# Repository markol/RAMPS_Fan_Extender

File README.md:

##Fan extension board for RAMPS##
This extension allows you to connect additional 4 fans into RAMPS board (plugged into servo pins). Board is single sided and was designed for home etching, uses THT and SMD soldering components. Make sure board dimensions (16x40mm) are not colliding with your actual setup. NPN transistors can be used as well instead of FET's. Voltage above 5V is provided by additional connector plug, reversed polarity may destory electronics.
Configuration process is similar to other boards, example [here](https://www.geeetech.com/wiki/index.php/Reprap_Ramps1.4_RRD_Fan_Extender), use pins 11, 6, 5 or 4. Made with KiCAD.

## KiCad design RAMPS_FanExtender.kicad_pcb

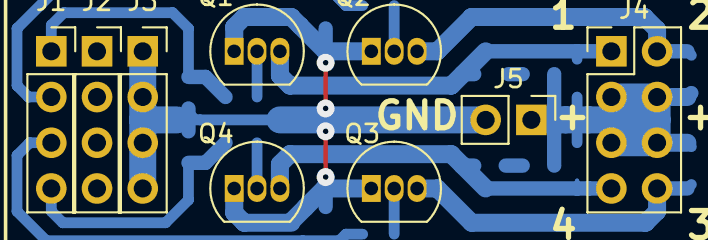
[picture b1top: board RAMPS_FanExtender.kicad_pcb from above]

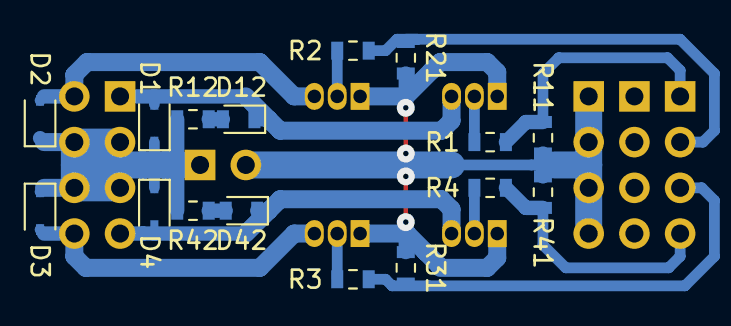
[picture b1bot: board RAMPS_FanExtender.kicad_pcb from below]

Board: 2 copper layers, 25 parts (16 on the bottom side), 16 nets.

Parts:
D1, D2, D3, D4: 1N4148WS; D_SOD-323
D12, D42: LED; LED_0603_1608Metric
J1: Conn_01; PinSocket_1x04_P2.54mm_Vertical
J2: Conn_02; PinSocket_1x04_P2.54mm_Vertical
J3: Conn_03; PinSocket_1x04_P2.54mm_Vertical
J4: Conn_FANS; PinHeader_2x04_P2.54mm_Vertical
J5: Conn_01x02; PinHeader_1x02_P2.54mm_Vertical
Q1, Q2, Q3, Q4: 2N7000; TO-92_Inline
R1, R2, R3, R4: 10R; R_0603_1608Metric
R11, R21, R31, R41: 100K; R_0603_1608Metric
R12, R42: 2K; R_0603_1608Metric

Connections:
+12V: D1.1, D2.1, D3.1, D4.1, J4.3, J4.4, J4.5, J4.6, J5.1, R12.2, R42.2
/FAN1_OUT: D1.2, D12.1, J4.1, Q1.3
/FAN1_PWM: J1.1, R1.2, R11.2
/FAN2_OUT: D2.2, J4.2, Q2.3
/FAN2_PWM: J1.2, R2.1, R21.1
/FAN3_OUT: D3.2, J4.8, Q3.3
/FAN3_PWM: J1.3, R3.2, R31.2
/FAN4_OUT: D4.2, D42.1, J4.7, Q4.3
/FAN4_PWM: J1.4, R4.1, R41.1
GND: J3.1, J3.2, J3.3, J3.4, J5.2, Q1.1, Q2.1, Q3.1, Q4.1, R11.1, R21.2, R31.1, R41.2
unnamed: D12.2, R12.1
unnamed: D42.2, R42.1
unnamed: Q1.2, R1.1
unnamed: Q2.2, R2.2
unnamed: Q3.2, R3.1
unnamed: Q4.2, R4.2

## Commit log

2018-04-02 Initial release.
